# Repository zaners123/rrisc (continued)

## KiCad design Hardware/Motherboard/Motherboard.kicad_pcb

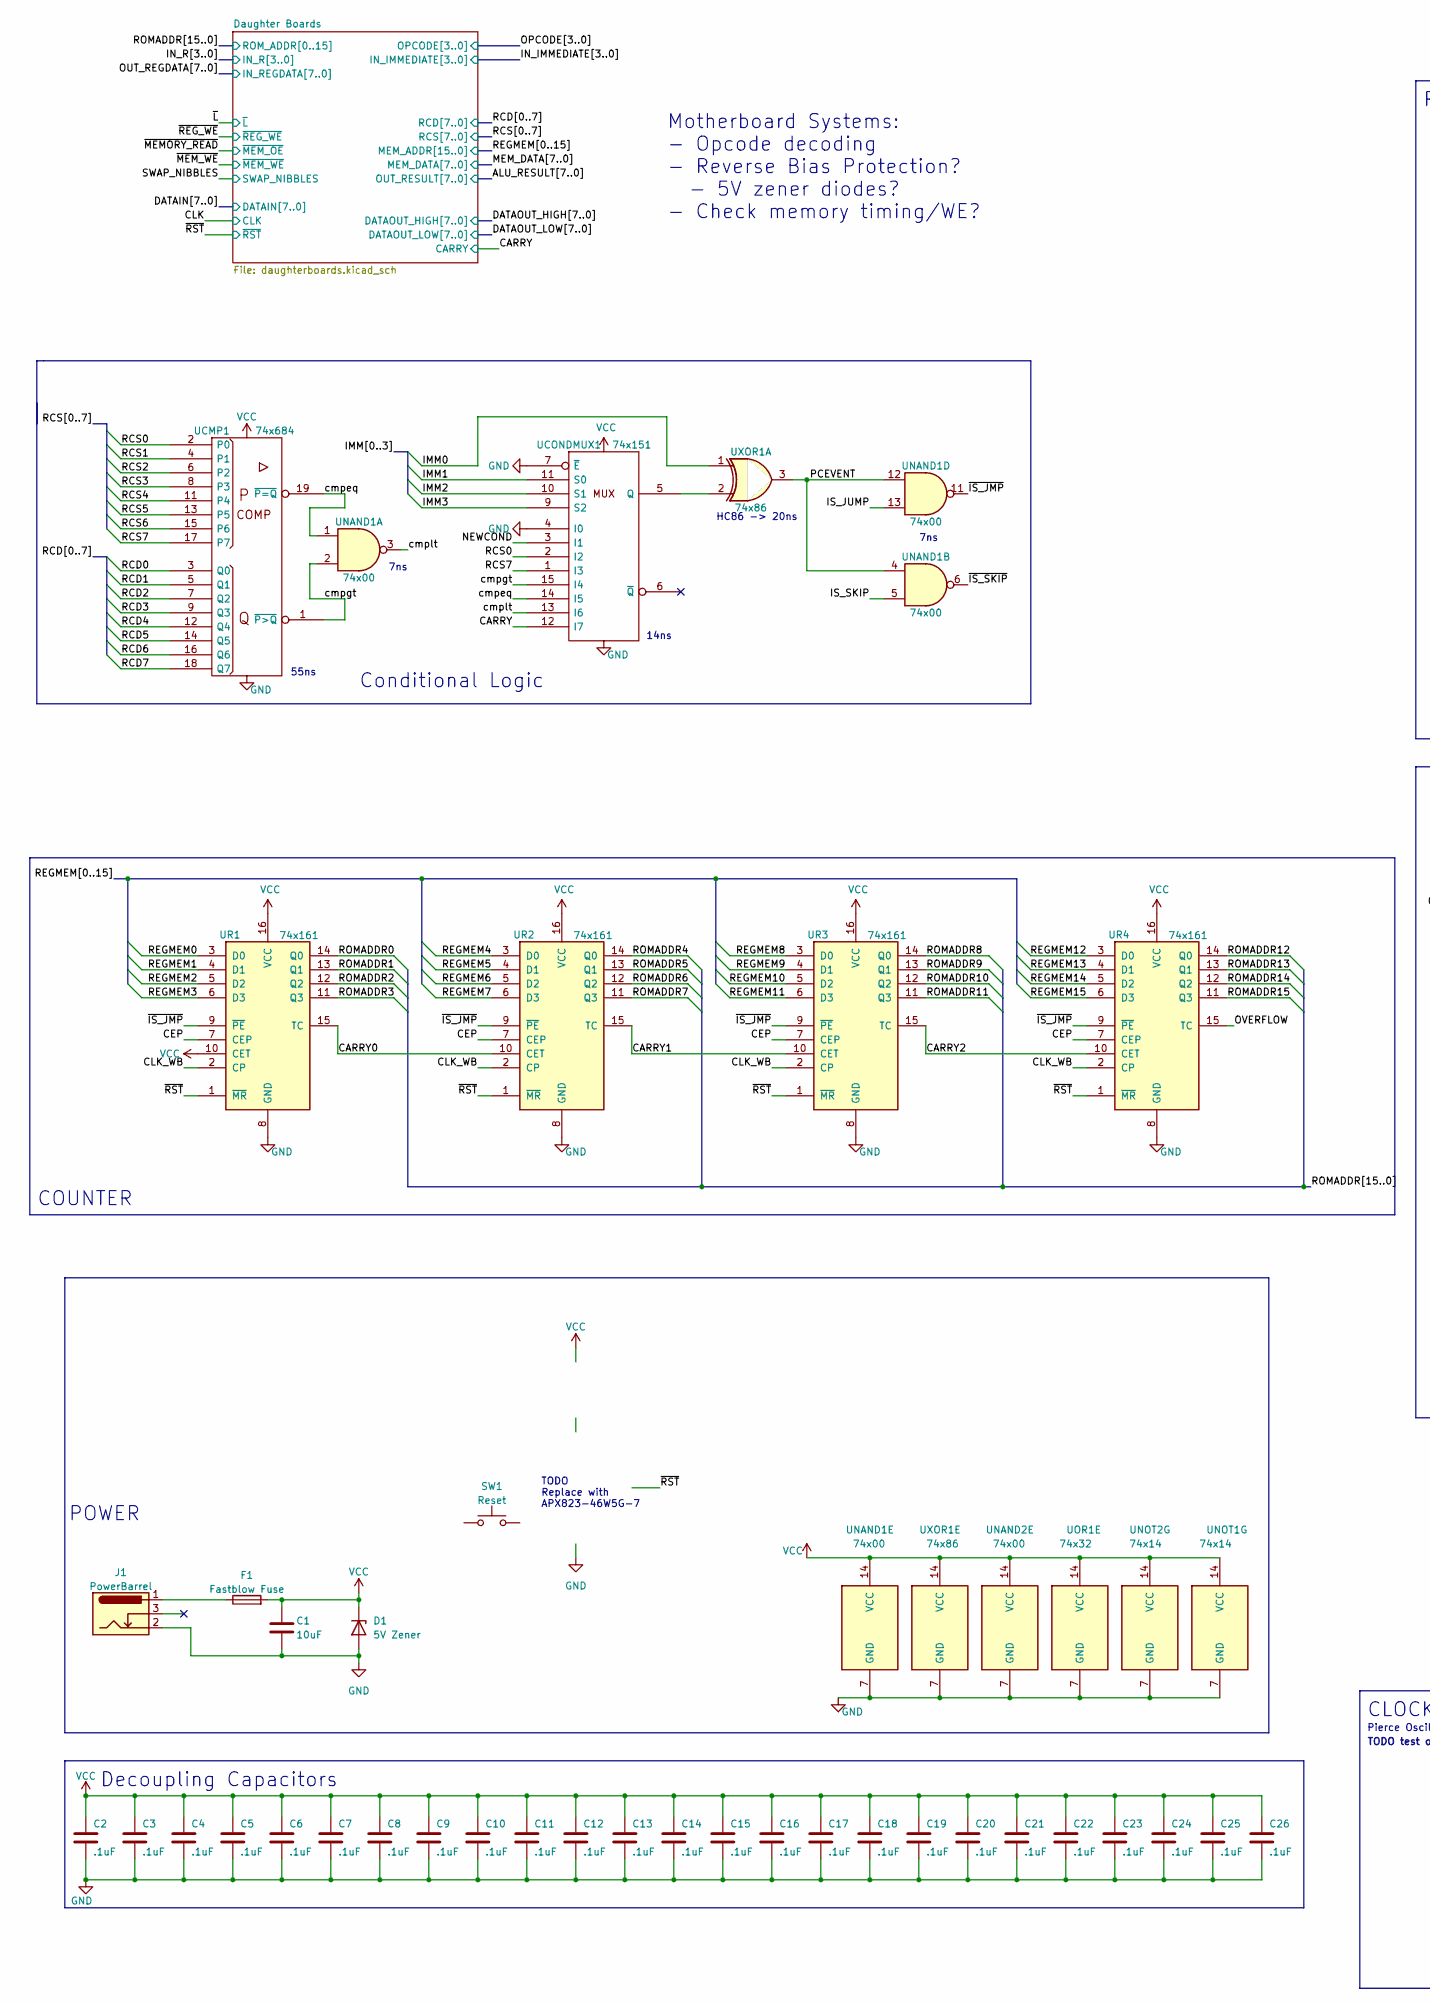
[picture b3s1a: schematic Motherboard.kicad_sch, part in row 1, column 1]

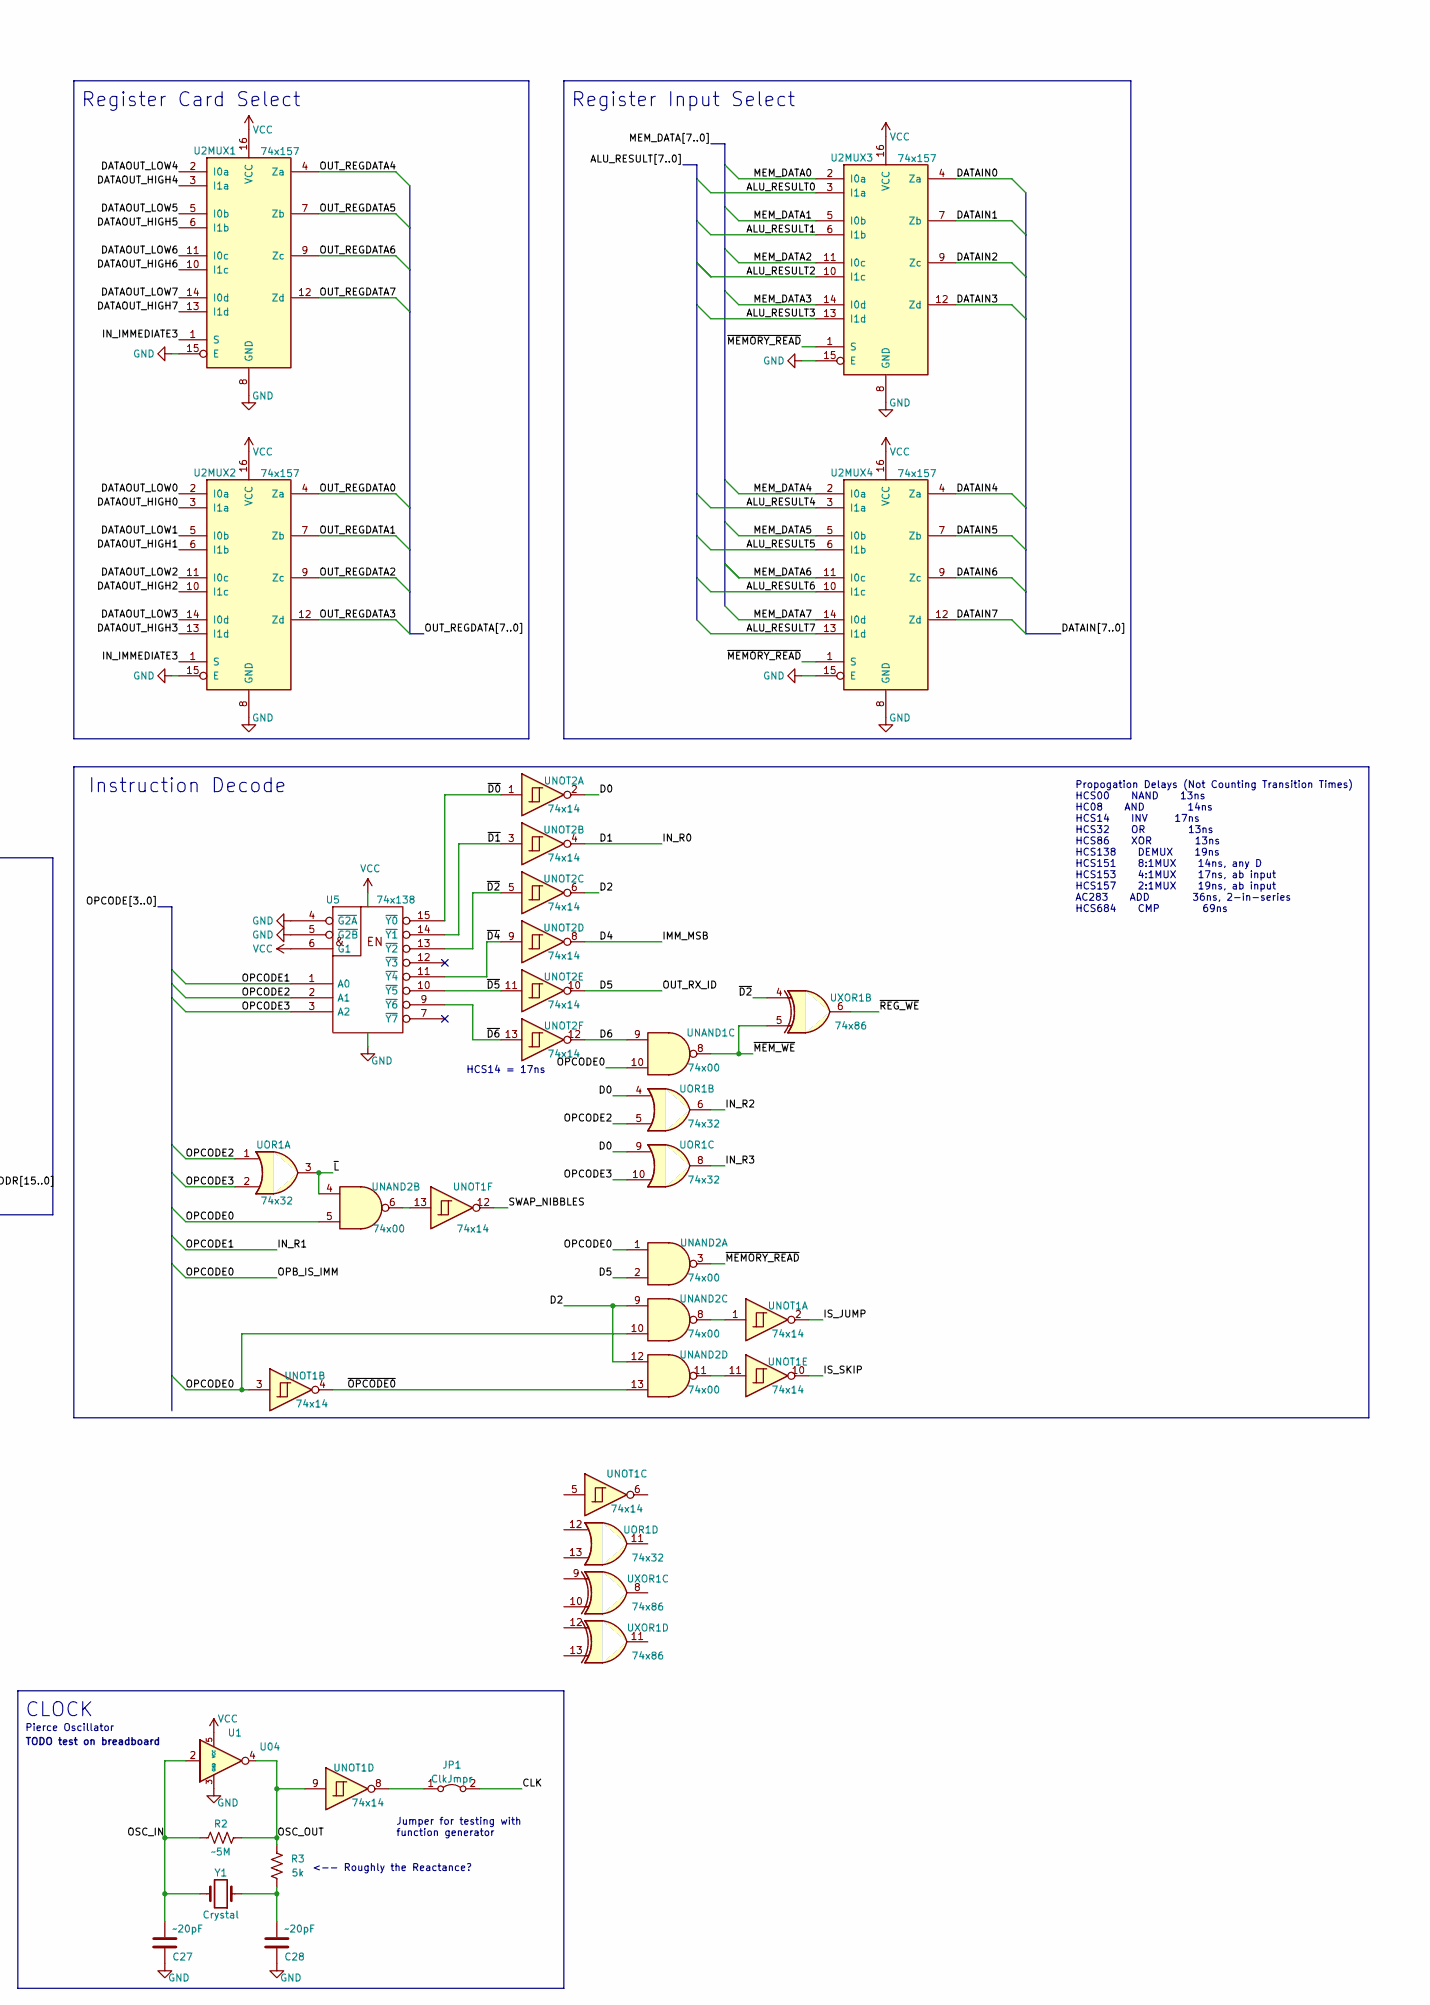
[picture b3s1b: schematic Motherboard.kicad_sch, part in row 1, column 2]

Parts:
C1: 10uF; C_1206_3216Metric_Pad1.33x1.80mm_HandSolder
C2, C3, C4, C5, C6, C7, C8, C9, C10, C11, C12, C13, C14, C15, C16, C17, C18, C19, C20, C21, C22, C23, C24, C25, C26: .1uF; C_1206_3216Metric_Pad1.33x1.80mm_HandSolder
C27, C28: ~20pF; C_Disc_D5.0mm_W2.5mm_P2.50mm
D1: 5V Zener
F1: Fastblow Fuse
J1: PowerBarrel; BarrelJack_Horizontal
JP1: ClkJmpr; PinHeader_1x02_P2.54mm_Vertical
R2: ~5M; R_1206_3216Metric_Pad1.30x1.75mm_HandSolder
R3: 5k; R_1206_3216Metric_Pad1.30x1.75mm_HandSolder
SW1: Reset; SW_PUSH_6mm_H5mm
U1: U04; TSOP5-CASE483
U2MUX1, U2MUX2, U2MUX3, U2MUX4: 74x157; D_R-PDSO-G16
U5: 74x138; R-PDSO-G16
UCMP1: 74x684; SOIC20_TI_DW0020A
UCONDMUX1: 74x151; D_R-PDSO-G16
UNAND1, UNAND2: 74x00; D_R-PDSO-G14
UNOT1, UNOT2: 74x14; D_R-PDSO-G14
UOR1: 74x32; D_R-PDSO-G14
UR1, UR2, UR3, UR4: 74x161; SOIC16-ONSEMI_751B-05_K
UXOR1: 74x86; D_R-PDSO-G14
Y1: Crystal; Crystal_HC49-4H_Vertical

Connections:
/ALU_RESULT0: U2MUX3.3 (I1a); also elsewhere on the board
/ALU_RESULT1: U2MUX3.6 (I1b); also elsewhere on the board
/ALU_RESULT2: U2MUX3.10 (I1c); also elsewhere on the board
/ALU_RESULT3: U2MUX3.13 (I1d); also elsewhere on the board
/ALU_RESULT4: U2MUX4.3 (I1a); also elsewhere on the board
/ALU_RESULT5: U2MUX4.6 (I1b); also elsewhere on the board
/ALU_RESULT6: U2MUX4.10 (I1c); also elsewhere on the board
/ALU_RESULT7: U2MUX4.13 (I1d); also elsewhere on the board
/CARRY0: UR1.15 (TC), UR2.10 (CET)
/CARRY1: UR2.15 (TC), UR3.10 (CET)
/CARRY2: UR3.15 (TC), UR4.10 (CET)
/CEP: UR1.7 (CEP), UR2.7 (CEP), UR3.7 (CEP), UR4.7 (CEP)
/CLK: JP1.2 (B); also elsewhere on the board
/CLK_WB: UR1.2 (CP), UR2.2 (CP), UR3.2 (CP), UR4.2 (CP)
/D0: UNOT2.2, UOR1.4, UOR1.9
/D2: UNAND2.9, UNAND2.12, UNOT2.6
/D4: UNOT2.8
/D5: UNAND2.2, UNOT2.10
/D6: UNAND1.9, UNOT2.12
/DATAIN0: U2MUX3.4 (Za); also elsewhere on the board
/DATAIN1: U2MUX3.7 (Zb); also elsewhere on the board
/DATAIN2: U2MUX3.9 (Zc); also elsewhere on the board
/DATAIN3: U2MUX3.12 (Zd); also elsewhere on the board
/DATAIN4: U2MUX4.4 (Za); also elsewhere on the board
/DATAIN5: U2MUX4.7 (Zb); also elsewhere on the board
/DATAIN6: U2MUX4.9 (Zc); also elsewhere on the board
/DATAIN7: U2MUX4.12 (Zd); also elsewhere on the board
/DATAOUT_HIGH0: U2MUX2.3 (I1a); also elsewhere on the board
/DATAOUT_HIGH1: U2MUX2.6 (I1b); also elsewhere on the board
/DATAOUT_HIGH2: U2MUX2.10 (I1c); also elsewhere on the board
/DATAOUT_HIGH3: U2MUX2.13 (I1d); also elsewhere on the board
/DATAOUT_HIGH4: U2MUX1.3 (I1a); also elsewhere on the board
/DATAOUT_HIGH5: U2MUX1.6 (I1b); also elsewhere on the board
/DATAOUT_HIGH6: U2MUX1.10 (I1c); also elsewhere on the board
/DATAOUT_HIGH7: U2MUX1.13 (I1d); also elsewhere on the board
/DATAOUT_LOW0: U2MUX2.2 (I0a); also elsewhere on the board
/DATAOUT_LOW1: U2MUX2.5 (I0b); also elsewhere on the board
/DATAOUT_LOW2: U2MUX2.11 (I0c); also elsewhere on the board
/DATAOUT_LOW3: U2MUX2.14 (I0d); also elsewhere on the board
/DATAOUT_LOW4: U2MUX1.2 (I0a); also elsewhere on the board
/DATAOUT_LOW5: U2MUX1.5 (I0b); also elsewhere on the board
/DATAOUT_LOW6: U2MUX1.11 (I0c); also elsewhere on the board
/DATAOUT_LOW7: U2MUX1.14 (I0d); also elsewhere on the board
/FLAG_CARRY: UCONDMUX1.12 (I7)
/IMM0: UXOR1.1
/IMM1: UCONDMUX1.11 (S0)
/IMM2: UCONDMUX1.10 (S1)
/IMM3: UCONDMUX1.9 (S2)
/IN_IMMEDIATE3: U2MUX1.1 (S), U2MUX2.1 (S); also elsewhere on the board
/IN_R0: UNOT2.4; also elsewhere on the board
/IN_R2: UOR1.6; also elsewhere on the board
/IN_R3: UOR1.8; also elsewhere on the board
/IS_JUMP: UNAND1.13, UNOT1.2
/IS_SKIP: UNAND1.5, UNOT1.10
/MEM_DATA0: U2MUX3.2 (I0a); also elsewhere on the board
/MEM_DATA1: U2MUX3.5 (I0b); also elsewhere on the board
/MEM_DATA2: U2MUX3.11 (I0c); also elsewhere on the board
/MEM_DATA3: U2MUX3.14 (I0d); also elsewhere on the board
/MEM_DATA4: U2MUX4.2 (I0a); also elsewhere on the board
/MEM_DATA5: U2MUX4.5 (I0b); also elsewhere on the board
/MEM_DATA6: U2MUX4.11 (I0c); also elsewhere on the board
/MEM_DATA7: U2MUX4.14 (I0d); also elsewhere on the board
/NEWCOND: UCONDMUX1.3 (I1)
/OPCODE0: UNAND1.10, UNAND2.1, UNAND2.5, UNAND2.10, UNOT1.3; also elsewhere on the board
/OPCODE2: U5.2 (A1), UOR1.1, UOR1.5; also elsewhere on the board
/OPCODE3: U5.3 (A2), UOR1.2, UOR1.10; also elsewhere on the board
/OSC_IN: C27.2, R2.1, U1.2, Y1.2
/OSC_OUT: R2.2, R3.2, U1.4, UNOT1.9
/OUT_REGDATA0: U2MUX2.4 (Za); also elsewhere on the board
/OUT_REGDATA1: U2MUX2.7 (Zb); also elsewhere on the board
/OUT_REGDATA2: U2MUX2.9 (Zc); also elsewhere on the board
/OUT_REGDATA3: U2MUX2.12 (Zd); also elsewhere on the board
/OUT_REGDATA4: U2MUX1.4 (Za); also elsewhere on the board
/OUT_REGDATA5: U2MUX1.7 (Zb); also elsewhere on the board
/OUT_REGDATA6: U2MUX1.9 (Zc); also elsewhere on the board
/OUT_REGDATA7: U2MUX1.12 (Zd); also elsewhere on the board
/OVERFLOW: UR4.15 (TC)
/PCEVENT: UNAND1.4, UNAND1.12, UXOR1.3
/RCD0: UCMP1.3 (Q0); also elsewhere on the board
/RCD1: UCMP1.5 (Q1); also elsewhere on the board
/RCD2: UCMP1.7 (Q2); also elsewhere on the board
/RCD3: UCMP1.9 (Q3); also elsewhere on the board
/RCD4: UCMP1.12 (Q4); also elsewhere on the board
/RCD5: UCMP1.14 (Q5); also elsewhere on the board
/RCD6: UCMP1.16 (Q6); also elsewhere on the board
/RCD7: UCMP1.18 (Q7); also elsewhere on the board
/RCS1: UCMP1.4 (P1); also elsewhere on the board
/RCS2: UCMP1.6 (P2); also elsewhere on the board
/RCS3: UCMP1.8 (P3); also elsewhere on the board
/RCS4: UCMP1.11 (P4); also elsewhere on the board
/RCS5: UCMP1.13 (P5); also elsewhere on the board
/RCS6: UCMP1.15 (P6); also elsewhere on the board
/REGMEM0: UR1.3 (D0); also elsewhere on the board
/REGMEM1: UR1.4 (D1); also elsewhere on the board
/REGMEM2: UR1.5 (D2); also elsewhere on the board
/REGMEM3: UR1.6 (D3); also elsewhere on the board
/REGMEM4: UR2.3 (D0); also elsewhere on the board
/REGMEM5: UR2.4 (D1); also elsewhere on the board
/REGMEM6: UR2.5 (D2); also elsewhere on the board
/REGMEM7: UR2.6 (D3); also elsewhere on the board
/REGMEM8: UR3.3 (D0); also elsewhere on the board
/REGMEM9: UR3.4 (D1); also elsewhere on the board
/REGMEM10: UR3.5 (D2); also elsewhere on the board
/REGMEM11: UR3.6 (D3); also elsewhere on the board
/REGMEM12: UR4.3 (D0); also elsewhere on the board
/REGMEM13: UR4.4 (D1); also elsewhere on the board
/REGMEM14: UR4.5 (D2); also elsewhere on the board
/REGMEM15: UR4.6 (D3); also elsewhere on the board
/ROMADDR0: UR1.14 (Q0); also elsewhere on the board
/ROMADDR1: UR1.13 (Q1); also elsewhere on the board
/ROMADDR2: UR1.12 (Q2); also elsewhere on the board
/ROMADDR3: UR1.11 (Q3); also elsewhere on the board
/ROMADDR4: UR2.14 (Q0); also elsewhere on the board
/ROMADDR5: UR2.13 (Q1); also elsewhere on the board
/ROMADDR6: UR2.12 (Q2); also elsewhere on the board
/ROMADDR7: UR2.11 (Q3); also elsewhere on the board
/ROMADDR8: UR3.14 (Q0); also elsewhere on the board
/ROMADDR9: UR3.13 (Q1); also elsewhere on the board
/ROMADDR10: UR3.12 (Q2); also elsewhere on the board
/ROMADDR11: UR3.11 (Q3); also elsewhere on the board
/ROMADDR12: UR4.14 (Q0); also elsewhere on the board
/ROMADDR13: UR4.13 (Q1); also elsewhere on the board
/ROMADDR14: UR4.12 (Q2); also elsewhere on the board
/ROMADDR15: UR4.11 (Q3); also elsewhere on the board
/SWAP_NIBBLES: UNOT1.12; also elsewhere on the board
/~D0: U5.15 (~Y0), UNOT2.1
/~D1: U5.14 (~Y1), UNOT2.3
/~D2: U5.13 (~Y2), UNOT2.5, UXOR1.4
/~D4: U5.11 (~Y4), UNOT2.9
/~D5: U5.10 (~Y5), UNOT2.11
/~D6: U5.9 (~Y6), UNOT2.13
/~IS_JMP: UNAND1.11, UR1.9 (~PE), UR2.9 (~PE), UR3.9 (~PE), UR4.9 (~PE)
/~IS_SKIP: UNAND1.6
/~L: UNAND2.4, UOR1.3; also elsewhere on the board
/~MEMORY_READ: U2MUX3.1 (S), U2MUX4.1 (S), UNAND2.3
/~MEM_WE: UNAND1.8, UXOR1.5
/~OPCODE0: UNAND2.13, UNOT1.4
/~REG_WE: UXOR1.6; also elsewhere on the board
/~RST: SW1.1, UR1.1 (~MR), UR2.1 (~MR), UR3.1 (~MR), UR4.1 (~MR); also elsewhere on the board
GND: C1.2, C2.2, C3.2, C4.2, C5.2, C6.2, C7.2, C8.2, C9.2, C10.2, C11.2, C12.2, C13.2, C14.2, C15.2, C16.2, C17.2, C18.2, C19.2, C20.2, C21.2, C22.2, C23.2, C24.2, C25.2, C26.2, C27.1, C28.1, D1.2 (A), J1.2, SW1.2, U1.3 (GND), U2MUX1.8 (GND), U2MUX1.15 (E), U2MUX2.8 (GND), U2MUX2.15 (E), U2MUX3.8 (GND), U2MUX3.15 (E), U2MUX4.8 (GND), U2MUX4.15 (E), U5.4 (~G2A), U5.5 (~G2B), U5.8 (GND), UCMP1.10 (Gnd), UCONDMUX1.4 (I0), UCONDMUX1.7 (~E), UCONDMUX1.8 (GND), UNAND1.7 (GND), UNAND2.7 (GND), UNOT1.7 (GND), UNOT2.7 (GND), UOR1.7 (GND), UR1.8 (GND), UR2.8 (GND), UR3.8 (GND), UR4.8 (GND), UXOR1.7 (GND); also elsewhere on the board
unnamed: C28.2, R3.1, Y1.1
unnamed: JP1.1 (A), UNOT1.8
unnamed: UCONDMUX1.5 (Q), UXOR1.2
unnamed: UNAND2.6, UNOT1.13
unnamed: UNAND2.8, UNOT1.1
unnamed: UNAND2.11, UNOT1.11

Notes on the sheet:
CLOCK
POWER
Register Input Select
COUNTER
HC86 -> 20ns
<-- Roughly the Reactance?
Instruction Decode
TODO Replace with APX823-46W5G-7
55ns
Jumper for testing with function generator
14ns
HCS14 = 17ns
Propogation Delays (Not Counting Transition Times) HCS00 NAND 13ns HC08 AND 14ns HCS14 INV 17ns HCS32 OR 13ns HCS86 XOR 13ns HCS138 DEMUX 19ns HCS151 8:1MUX 14ns, any D HCS153 4:1MUX 17ns, ab input HCS157 2:1MUX 19ns, ab input AC283 ADD 36ns, 2-in-series HCS684 CMP 69ns
7ns
Motherboard Systems: - Opcode decoding - Reverse Bias Protection? - 5V zener diodes? - Check memory timing/WE?
Register Card Select
Conditional Logic
Pierce Oscillator
Decoupling Capacitors
TODO test on breadboard

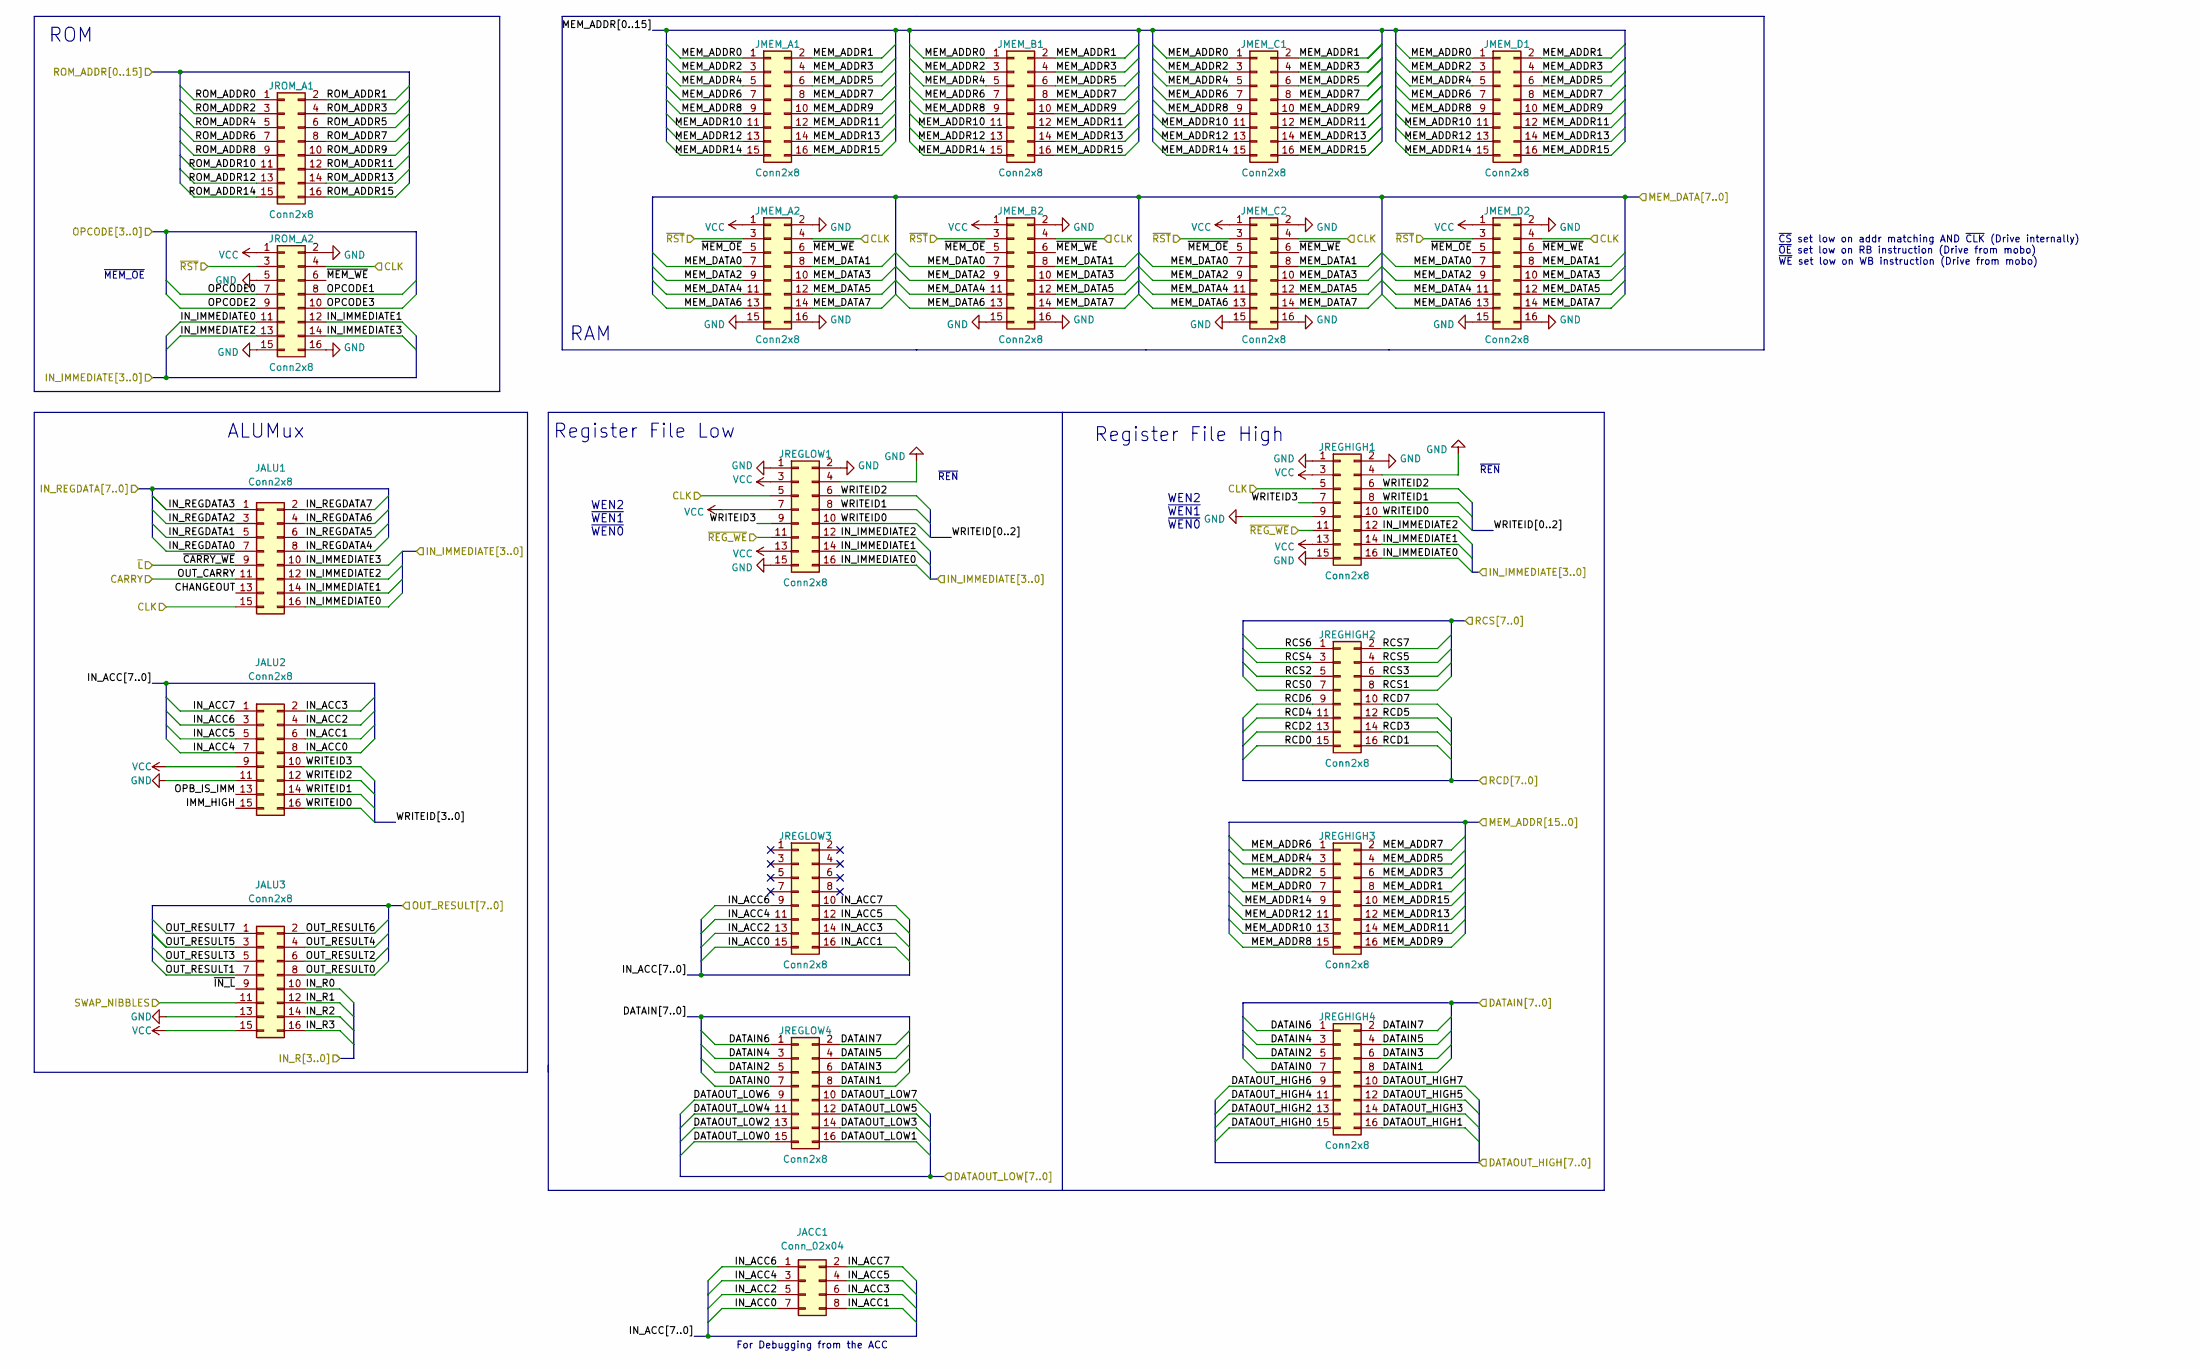
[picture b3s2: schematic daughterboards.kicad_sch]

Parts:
JACC1: Conn_02x04; PinHeader_2x04_P2.54mm_Vertical
JALU1, JALU2, JALU3: Conn2x8; PinSocket_2x08_P2.54mm_Vertical
JMEM_A1, JMEM_A2: Conn2x8; PinSocket_2x08_P2.54mm_Vertical
JMEM_B1, JMEM_B2: Conn2x8; PinSocket_2x08_P2.54mm_Vertical
JMEM_C1, JMEM_C2: Conn2x8; PinSocket_2x08_P2.54mm_Vertical
JMEM_D1, JMEM_D2: Conn2x8; PinSocket_2x08_P2.54mm_Vertical
JREGHIGH1, JREGHIGH2, JREGHIGH3, JREGHIGH4: Conn2x8; PinSocket_2x08_P2.54mm_Vertical
JREGLOW1, JREGLOW3, JREGLOW4: Conn2x8; PinSocket_2x08_P2.54mm_Vertical
JROM_A1, JROM_A2: Conn2x8; PinSocket_2x08_P2.54mm_Vertical

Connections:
/ALU_RESULT0: JALU3.8; also elsewhere on the board
/ALU_RESULT1: JALU3.7; also elsewhere on the board
/ALU_RESULT2: JALU3.6; also elsewhere on the board
/ALU_RESULT3: JALU3.5; also elsewhere on the board
/ALU_RESULT4: JALU3.4; also elsewhere on the board
/ALU_RESULT5: JALU3.3; also elsewhere on the board
/ALU_RESULT6: JALU3.2; also elsewhere on the board
/ALU_RESULT7: JALU3.1; also elsewhere on the board
/CLK: JALU1.15, JMEM_A2.4, JMEM_B2.4, JMEM_C2.4, JMEM_D2.4, JREGHIGH1.5, JREGLOW1.5, JROM_A2.4; also elsewhere on the board
/DATAIN0: JREGHIGH4.7, JREGLOW4.7; also elsewhere on the board
/DATAIN1: JREGHIGH4.8, JREGLOW4.8; also elsewhere on the board
/DATAIN2: JREGHIGH4.5, JREGLOW4.5; also elsewhere on the board
/DATAIN3: JREGHIGH4.6, JREGLOW4.6; also elsewhere on the board
/DATAIN4: JREGHIGH4.3, JREGLOW4.3; also elsewhere on the board
/DATAIN5: JREGHIGH4.4, JREGLOW4.4; also elsewhere on the board
/DATAIN6: JREGHIGH4.1, JREGLOW4.1; also elsewhere on the board
/DATAIN7: JREGHIGH4.2, JREGLOW4.2; also elsewhere on the board
/DATAOUT_HIGH0: JREGHIGH4.15; also elsewhere on the board
/DATAOUT_HIGH1: JREGHIGH4.16; also elsewhere on the board
/DATAOUT_HIGH2: JREGHIGH4.13; also elsewhere on the board
/DATAOUT_HIGH3: JREGHIGH4.14; also elsewhere on the board
/DATAOUT_HIGH4: JREGHIGH4.11; also elsewhere on the board
/DATAOUT_HIGH5: JREGHIGH4.12; also elsewhere on the board
/DATAOUT_HIGH6: JREGHIGH4.9; also elsewhere on the board
/DATAOUT_HIGH7: JREGHIGH4.10; also elsewhere on the board
/DATAOUT_LOW0: JREGLOW4.15; also elsewhere on the board
/DATAOUT_LOW1: JREGLOW4.16; also elsewhere on the board
/DATAOUT_LOW2: JREGLOW4.13; also elsewhere on the board
/DATAOUT_LOW3: JREGLOW4.14; also elsewhere on the board
/DATAOUT_LOW4: JREGLOW4.11; also elsewhere on the board
/DATAOUT_LOW5: JREGLOW4.12; also elsewhere on the board
/DATAOUT_LOW6: JREGLOW4.9; also elsewhere on the board
/DATAOUT_LOW7: JREGLOW4.10; also elsewhere on the board
/Daughter Boards/CHANGEOUT: JALU1.13
/Daughter Boards/IMM_HIGH: JALU2.15
/Daughter Boards/IN_ACC0: JACC1.7, JALU2.8, JREGLOW3.15
/Daughter Boards/IN_ACC1: JACC1.8, JALU2.6, JREGLOW3.16
/Daughter Boards/IN_ACC2: JACC1.5, JALU2.4, JREGLOW3.13
/Daughter Boards/IN_ACC3: JACC1.6, JALU2.2, JREGLOW3.14
/Daughter Boards/IN_ACC4: JACC1.3, JALU2.7, JREGLOW3.11
/Daughter Boards/IN_ACC5: JACC1.4, JALU2.5, JREGLOW3.12
/Daughter Boards/IN_ACC6: JACC1.1, JALU2.3, JREGLOW3.9
/Daughter Boards/IN_ACC7: JACC1.2, JALU2.1, JREGLOW3.10
/Daughter Boards/OPB_IS_IMM: JALU2.13
/Daughter Boards/OUT_CARRY: JALU1.11
/Daughter Boards/WRITEID0: JALU2.16, JREGHIGH1.10, JREGLOW1.10
/Daughter Boards/WRITEID1: JALU2.14, JREGHIGH1.8, JREGLOW1.8
/Daughter Boards/WRITEID2: JALU2.12, JREGHIGH1.6, JREGLOW1.6
/Daughter Boards/WRITEID3: JALU2.10, JREGHIGH1.7, JREGLOW1.9
/Daughter Boards/~IN_L: JALU3.9
/Daughter Boards/~MEM_OE: JMEM_A2.5, JMEM_B2.5, JMEM_C2.5, JMEM_D2.5
/Daughter Boards/~MEM_WE: JMEM_A2.6, JMEM_B2.6, JMEM_C2.6, JMEM_D2.6, JROM_A2.6
/IN_IMMEDIATE0: JALU1.16, JREGHIGH1.16, JREGLOW1.16, JROM_A2.11
/IN_IMMEDIATE1: JALU1.14, JREGHIGH1.14, JREGLOW1.14, JROM_A2.12
/IN_IMMEDIATE2: JALU1.12, JREGHIGH1.12, JREGLOW1.12, JROM_A2.13
/IN_IMMEDIATE3: JALU1.10, JROM_A2.14; also elsewhere on the board
/IN_R0: JALU3.10; also elsewhere on the board
/IN_R1: JALU3.12, JROM_A2.8
/IN_R2: JALU3.14; also elsewhere on the board
/IN_R3: JALU3.16; also elsewhere on the board
/MEM_DATA0: JMEM_A2.7, JMEM_B2.7, JMEM_C2.7, JMEM_D2.7; also elsewhere on the board
/MEM_DATA1: JMEM_A2.8, JMEM_B2.8, JMEM_C2.8, JMEM_D2.8; also elsewhere on the board
/MEM_DATA2: JMEM_A2.9, JMEM_B2.9, JMEM_C2.9, JMEM_D2.9; also elsewhere on the board
/MEM_DATA3: JMEM_A2.10, JMEM_B2.10, JMEM_C2.10, JMEM_D2.10; also elsewhere on the board
/MEM_DATA4: JMEM_A2.11, JMEM_B2.11, JMEM_C2.11, JMEM_D2.11; also elsewhere on the board
/MEM_DATA5: JMEM_A2.12, JMEM_B2.12, JMEM_C2.12, JMEM_D2.12; also elsewhere on the board
/MEM_DATA6: JMEM_A2.13, JMEM_B2.13, JMEM_C2.13, JMEM_D2.13; also elsewhere on the board
/MEM_DATA7: JMEM_A2.14, JMEM_B2.14, JMEM_C2.14, JMEM_D2.14; also elsewhere on the board
/OPCODE0: JROM_A2.7; also elsewhere on the board
/OPCODE2: JROM_A2.9; also elsewhere on the board
/OPCODE3: JROM_A2.10; also elsewhere on the board
/OUT_REGDATA0: JALU1.7; also elsewhere on the board
/OUT_REGDATA1: JALU1.5; also elsewhere on the board
/OUT_REGDATA2: JALU1.3; also elsewhere on the board
/OUT_REGDATA3: JALU1.1; also elsewhere on the board
/OUT_REGDATA4: JALU1.8; also elsewhere on the board
/OUT_REGDATA5: JALU1.6; also elsewhere on the board
/OUT_REGDATA6: JALU1.4; also elsewhere on the board
/OUT_REGDATA7: JALU1.2; also elsewhere on the board
/RCD0: JREGHIGH2.15; also elsewhere on the board
/RCD1: JREGHIGH2.16; also elsewhere on the board
/RCD2: JREGHIGH2.13; also elsewhere on the board
/RCD3: JREGHIGH2.14; also elsewhere on the board
/RCD4: JREGHIGH2.11; also elsewhere on the board
/RCD5: JREGHIGH2.12; also elsewhere on the board
/RCD6: JREGHIGH2.9; also elsewhere on the board
/RCD7: JREGHIGH2.10; also elsewhere on the board
/RCS1: JREGHIGH2.8; also elsewhere on the board
/RCS2: JREGHIGH2.5; also elsewhere on the board
/RCS3: JREGHIGH2.6; also elsewhere on the board
/RCS4: JREGHIGH2.3; also elsewhere on the board
/RCS5: JREGHIGH2.4; also elsewhere on the board
/RCS6: JREGHIGH2.1; also elsewhere on the board
/REGMEM0: JMEM_A1.1, JMEM_B1.1, JMEM_C1.1, JMEM_D1.1, JREGHIGH3.7; also elsewhere on the board
/REGMEM1: JMEM_A1.2, JMEM_B1.2, JMEM_C1.2, JMEM_D1.2, JREGHIGH3.8; also elsewhere on the board
/REGMEM2: JMEM_A1.3, JMEM_B1.3, JMEM_C1.3, JMEM_D1.3, JREGHIGH3.5; also elsewhere on the board
/REGMEM3: JMEM_A1.4, JMEM_B1.4, JMEM_C1.4, JMEM_D1.4, JREGHIGH3.6; also elsewhere on the board
/REGMEM4: JMEM_A1.5, JMEM_B1.5, JMEM_C1.5, JMEM_D1.5, JREGHIGH3.3; also elsewhere on the board
/REGMEM5: JMEM_A1.6, JMEM_B1.6, JMEM_C1.6, JMEM_D1.6, JREGHIGH3.4; also elsewhere on the board
/REGMEM6: JMEM_A1.7, JMEM_B1.7, JMEM_C1.7, JMEM_D1.7, JREGHIGH3.1; also elsewhere on the board
/REGMEM7: JMEM_A1.8, JMEM_B1.8, JMEM_C1.8, JMEM_D1.8, JREGHIGH3.2; also elsewhere on the board
/REGMEM8: JMEM_A1.9, JMEM_B1.9, JMEM_C1.9, JMEM_D1.9, JREGHIGH3.15; also elsewhere on the board
/REGMEM9: JMEM_A1.10, JMEM_B1.10, JMEM_C1.10, JMEM_D1.10, JREGHIGH3.16; also elsewhere on the board
/REGMEM10: JMEM_A1.11, JMEM_B1.11, JMEM_C1.11, JMEM_D1.11, JREGHIGH3.13; also elsewhere on the board
/REGMEM11: JMEM_A1.12, JMEM_B1.12, JMEM_C1.12, JMEM_D1.12, JREGHIGH3.14; also elsewhere on the board
/REGMEM12: JMEM_A1.13, JMEM_B1.13, JMEM_C1.13, JMEM_D1.13, JREGHIGH3.11; also elsewhere on the board
/REGMEM13: JMEM_A1.14, JMEM_B1.14, JMEM_C1.14, JMEM_D1.14, JREGHIGH3.12; also elsewhere on the board
/REGMEM14: JMEM_A1.15, JMEM_B1.15, JMEM_C1.15, JMEM_D1.15, JREGHIGH3.9; also elsewhere on the board
/REGMEM15: JMEM_A1.16, JMEM_B1.16, JMEM_C1.16, JMEM_D1.16, JREGHIGH3.10; also elsewhere on the board
/ROMADDR0: JROM_A1.1; also elsewhere on the board
/ROMADDR1: JROM_A1.2; also elsewhere on the board
/ROMADDR2: JROM_A1.3; also elsewhere on the board
/ROMADDR3: JROM_A1.4; also elsewhere on the board
/ROMADDR4: JROM_A1.5; also elsewhere on the board
/ROMADDR5: JROM_A1.6; also elsewhere on the board
/ROMADDR6: JROM_A1.7; also elsewhere on the board
/ROMADDR7: JROM_A1.8; also elsewhere on the board
/ROMADDR8: JROM_A1.9; also elsewhere on the board
/ROMADDR9: JROM_A1.10; also elsewhere on the board
/ROMADDR10: JROM_A1.11; also elsewhere on the board
/ROMADDR11: JROM_A1.12; also elsewhere on the board
/ROMADDR12: JROM_A1.13; also elsewhere on the board
/ROMADDR13: JROM_A1.14; also elsewhere on the board
/ROMADDR14: JROM_A1.15; also elsewhere on the board
/ROMADDR15: JROM_A1.16; also elsewhere on the board
/SWAP_NIBBLES: JALU3.11; also elsewhere on the board
/~L: JALU1.9; also elsewhere on the board
/~REG_WE: JREGHIGH1.11, JREGLOW1.11; also elsewhere on the board
/~RST: JMEM_A2.3, JMEM_B2.3, JMEM_C2.3, JMEM_D2.3, JROM_A2.3; also elsewhere on the board
GND: JALU2.11, JALU3.13, JMEM_A2.2, JMEM_A2.15, JMEM_A2.16, JMEM_B2.2, JMEM_B2.15, JMEM_B2.16, JMEM_C2.2, JMEM_C2.15, JMEM_C2.16, JMEM_D2.2, JMEM_D2.15, JMEM_D2.16, JREGHIGH1.1, JREGHIGH1.2, JREGHIGH1.4, JREGHIGH1.9, JREGHIGH1.15, JREGLOW1.1, JREGLOW1.2, JREGLOW1.4, JREGLOW1.15, JROM_A2.2, JROM_A2.5, JROM_A2.15, JROM_A2.16; also elsewhere on the board

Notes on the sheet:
WEN2 ~{WEN1} ~{WEN0}
For Debugging from the ACC
~{REN}
Register File High
ALUMux
RAM
ROM
Register File Low
~{MEM_OE}
~{CS} set low on addr matching AND ~{CLK} (Drive internally) ~{OE} set low on RB instruction (Drive from mobo) ~{WE} set low on WB instruction (Drive from mobo)

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
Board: 4 copper layers, 73 parts (29 on the bottom side), 157 nets, no tracks yet.

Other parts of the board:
R1: 10k; R_1206_3216Metric_Pad1.30x1.75mm_HandSolder

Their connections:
/~RST: R1.2; also elsewhere on the board
